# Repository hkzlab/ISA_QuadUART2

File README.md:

# ISA Quad UART Adapter (2 + 2)

## Introduction

This 8-bit ISA board will provide 4 serial RS232 ports using a single 16C554 controller.

Port 1 and 2 are exposed on the bracked as DB9 male connectors. Port 3 and 4 are internal.

IRQs will be shared between port 1/3 and port 2/4.

### Disclaimer

I take NO responsibility for what happens if you decide to build and use this card. Your computer might crash, catch fire or be destroyed in other nasty ways.
You're encourauged to take what you deem fit from this, and use it in your projects!

## Configuration

This board is configured via two blocks of jumpers:

```text
    .... SER4 
    ....
    .... SER3
IIII2323
RRRREEFF
QQQQ8888
3457
........ SER2
........
........ SER1
```

The upper block will select the address for port 3 (first row) and port 4 (third row). To select an address, you need to bridge the middle row at the specified address with the top or bottom row (depending on which port you wish to assign that address).

The bottom block selects the address for ports 1 and 2, and the IRQs for ports 1/3 and 2/4. The principle is the same.

Default configuration is as follow:
```text
    |... SER4 
    ||..
    .|.. SER3
IIII2323
RRRREEFF
QQQQ8888
3457
|.....|. SER2
||....||
.|.....| SER1
```

Which will assign 0x3F8 to port 1, 0x2F8 to port 2, 0x3E8 to port 3 and 0x2E8 to port 4.
Port 1/3 will get IRQ4 and port 2/4 will get IRQ3.

## Bill of Materials

- 4x 10uF / 25v capacitors
- 13x 100nF / 25v ceramic capacitors
- 1x 9-pin 10k bussed resistor network (RN3)
- 1x 5-pin 10k bussed resistor network (RN2)
- 1x 1.8432Mhz DIP14 or DIP8 oscillator
- 2x DB9 right angle, male, PCB mount connector
- 1x 1x20pin 2.54mm straight header strip (you will cut this as needed)
- 1x 2x20pin 2.54mm straight header strip (you will cut this as needed)
- 1x 2x20pin 2.54mm angled header strip (you will cut this as needed)
- 4x 75C185 RS232 drivers (U5, U6, U25, U26)
- 2x 74HCT138 (U1, U2)
- 1x 74HCT32 (U24)
- 1x 74HCT21 (U30)
- 1x 74HCT245 (U29) (with some controllers, like TL16C554, I noticed improved stability by using a 74LS245)
- 1x SC16C654, ST16C554 (U23) (all the 16C554 / 16C654 should be compatible, but to get TL16C554 working properly I had to replace U29) 
- Jumpers for board configuration
- Keystone 9200-15 bracket
- 1x PLCC68 THT socket
 
## Credits

- Thanks to [@A-Small-Mice](https://github.com/A-Small-Mice) for the printable bracket

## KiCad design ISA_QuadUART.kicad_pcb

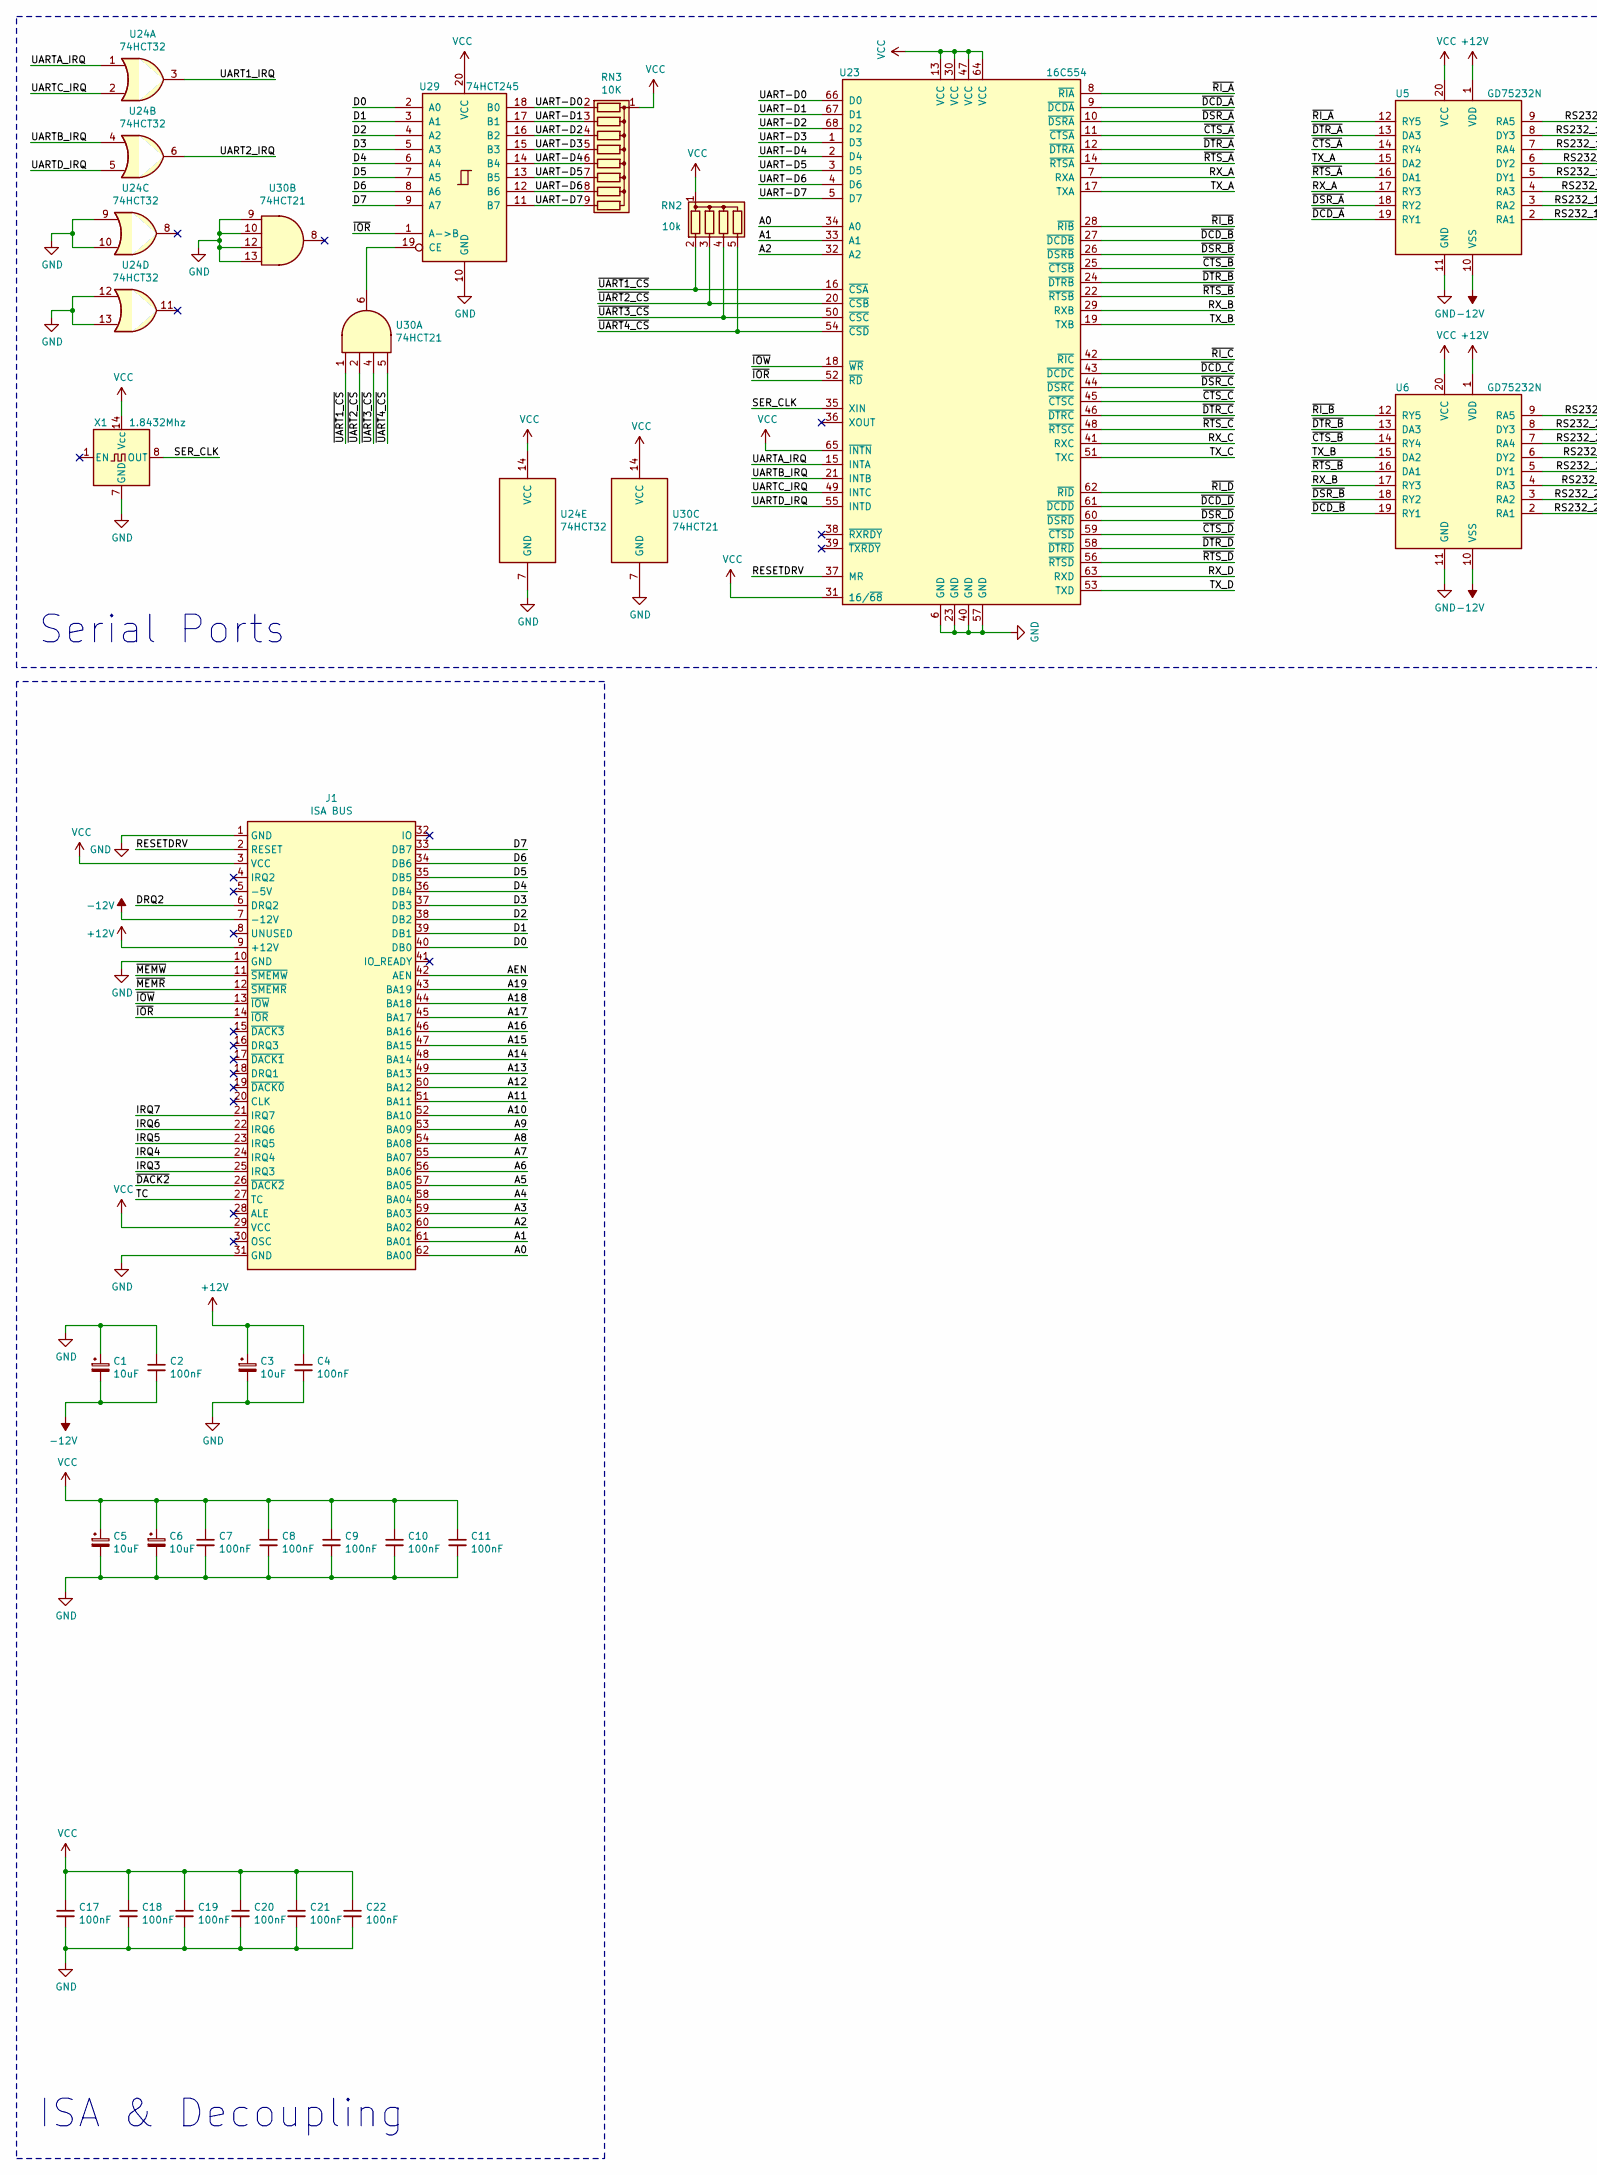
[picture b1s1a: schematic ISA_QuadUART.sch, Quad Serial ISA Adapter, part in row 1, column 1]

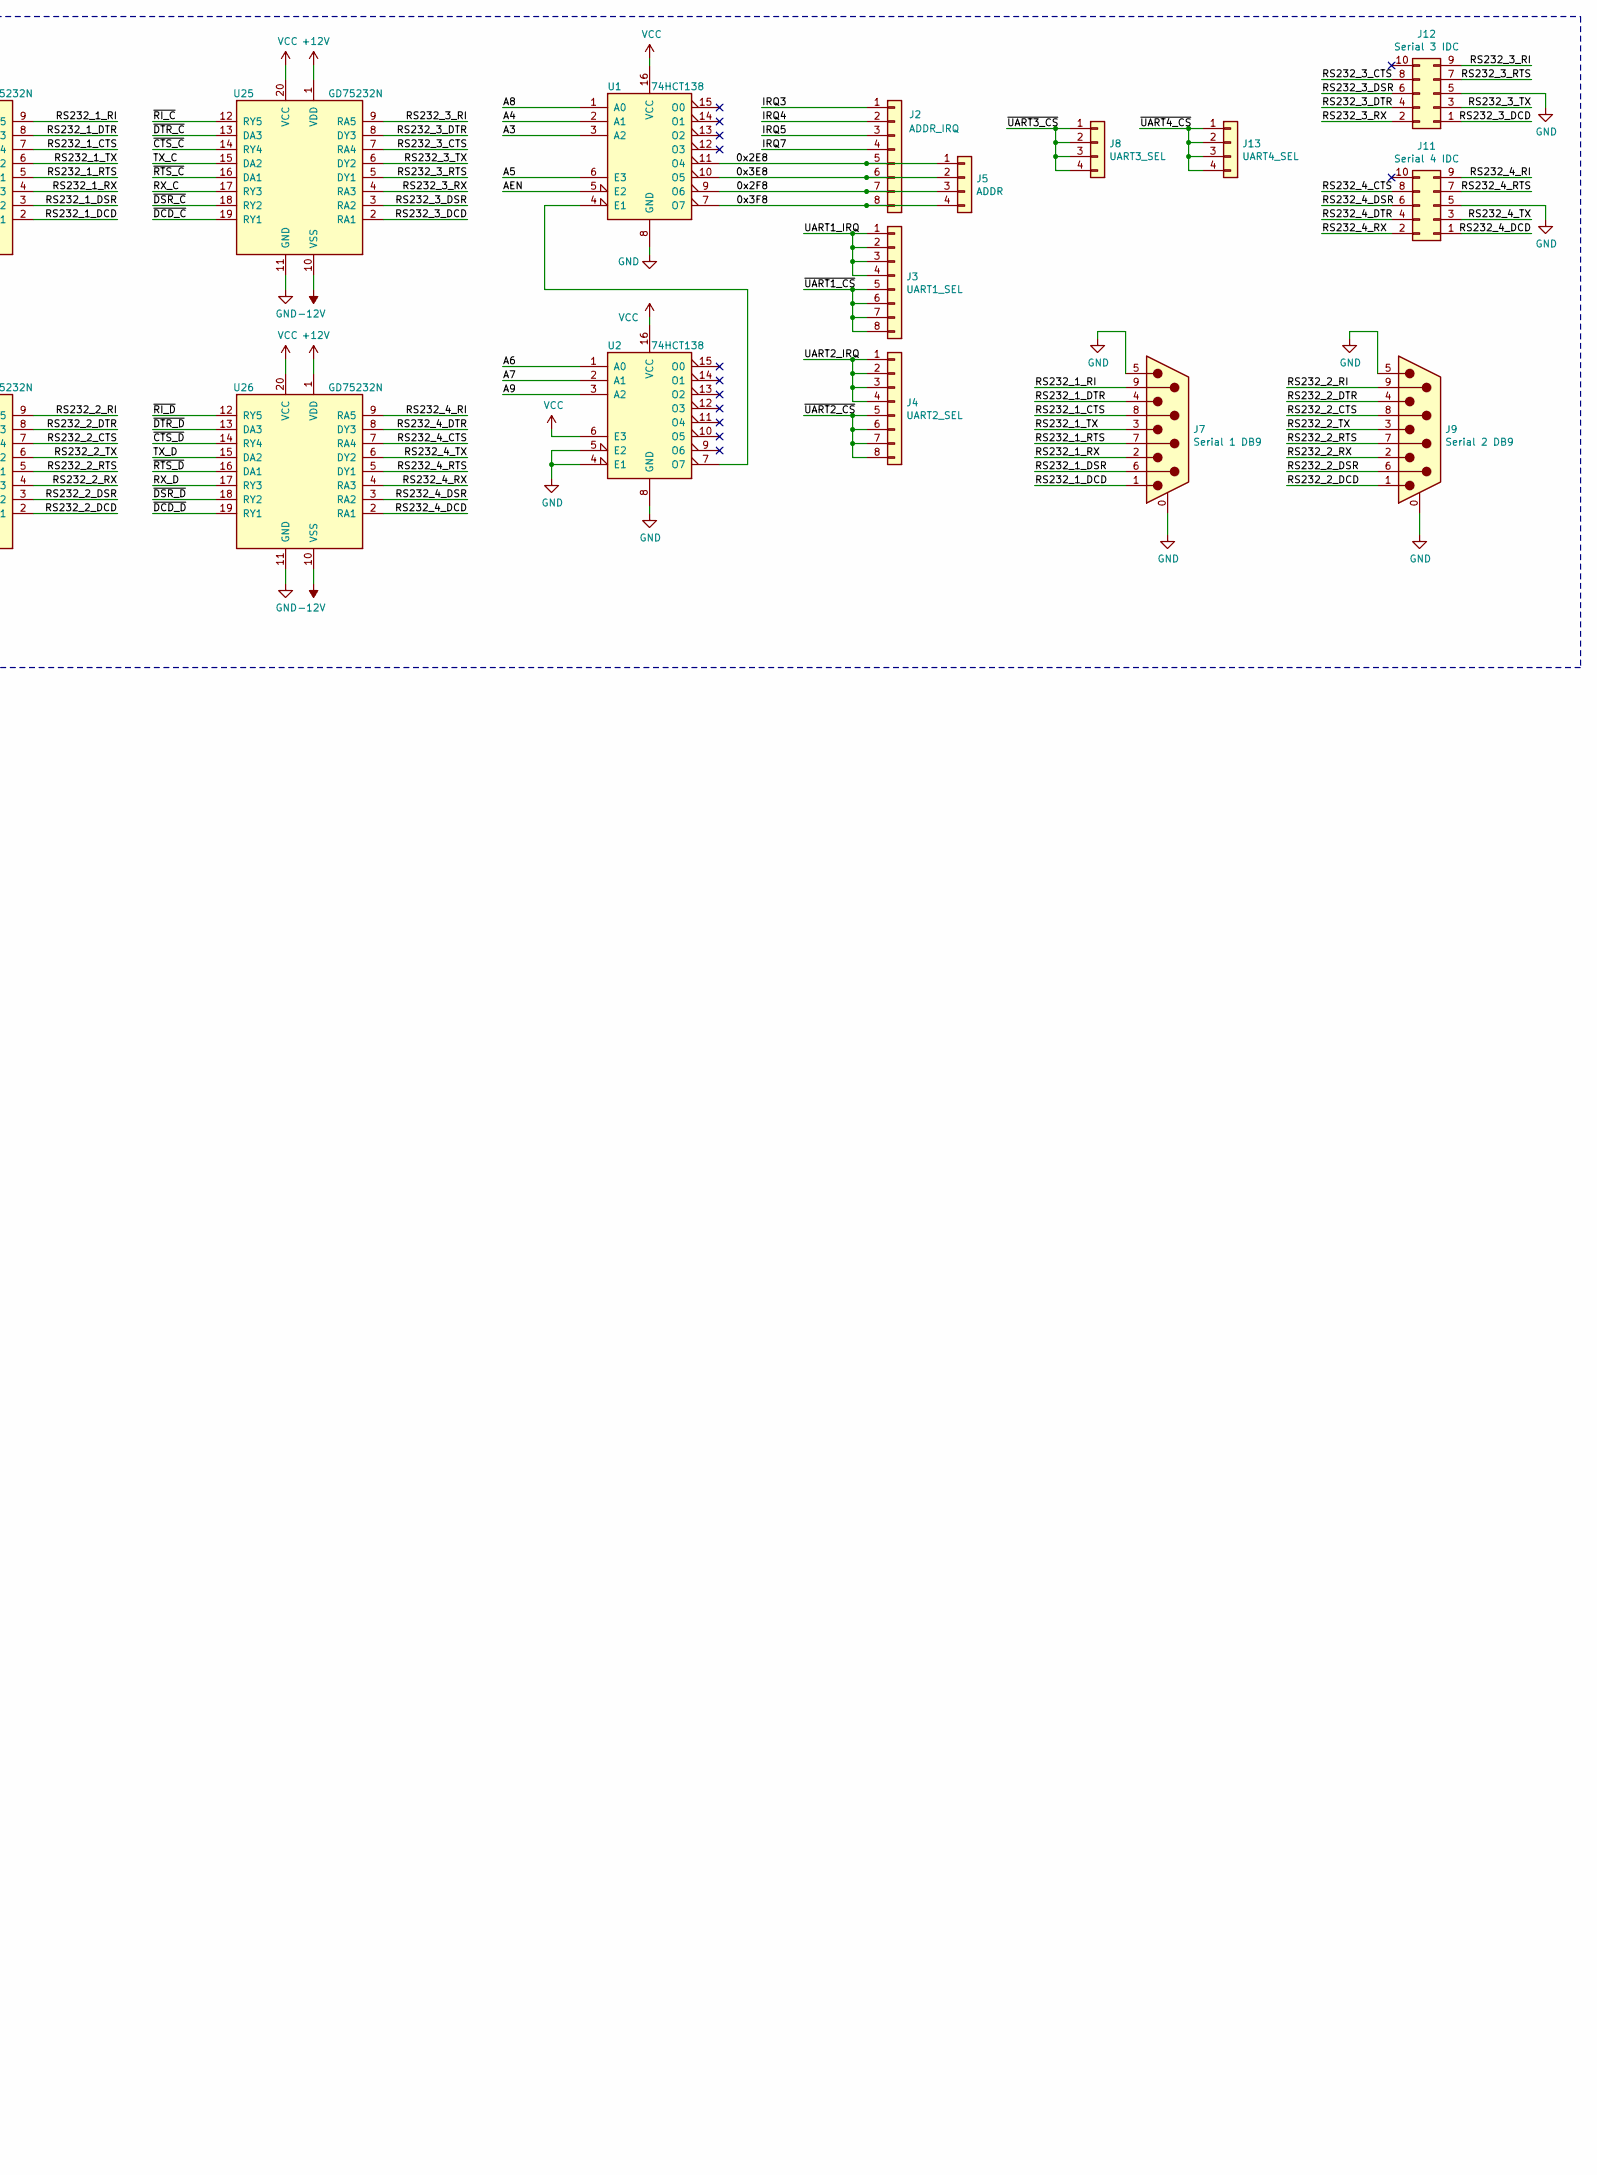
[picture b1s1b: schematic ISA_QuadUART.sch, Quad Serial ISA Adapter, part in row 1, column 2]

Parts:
C1, C3, C5, C6: 10uF; CP_Radial_D5.0mm_P2.50mm
C2, C4, C7, C8, C9, C10, C11, C17, C18, C19, C20, C21, C22: 100nF; C_Disc_D6.0mm_W2.5mm_P5.00mm
J1: ISA BUS; Conn_Edge_PCB_ISA8
J2: ADDR_IRQ; PinHeader_1x08_P2.54mm_Vertical
J3: UART1_SEL; PinHeader_1x08_P2.54mm_Vertical
J4: UART2_SEL; PinHeader_1x08_P2.54mm_Vertical
J5: ADDR; PinHeader_1x04_P2.54mm_Vertical
J7: Serial 1 DB9; DSUB-9_Male_Horizontal_P2.77x2.84mm_EdgePinOffset7.70mm_Hou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
J8: UART3_SEL; PinHeader_1x04_P2.54mm_Vertical
J9: Serial 2 DB9; DSUB-9_Male_Horizontal_P2.77x2.84mm_EdgePinOffset7.70mm_Hou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
J11: Serial 4 IDC; PinHeader_2x05_P2.54mm_Vertical
J12: Serial 3 IDC; PinHeader_2x05_P2.54mm_Vertical
J13: UART4_SEL; PinHeader_1x04_P2.54mm_Vertical
RN2: 10k; R_Array_SIP5
RN3: 10K; R_Array_SIP9
U1, U2: 74HCT138; DIP-16_W7.62mm_LongPads
U5, U6, U25, U26: GD75232N; DIP-20_W7.62mm_LongPads
U23: 16C554; PLCC-68_THT-Socket
U24: 74HCT32; DIP-14_W7.62mm_LongPads
U29: 74HCT245; DIP-20_W7.62mm_LongPads
U30: 74HCT21; DIP-14_W7.62mm_LongPads
X1: 1.8432Mhz; Oscillator_DIP-14-8

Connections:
+12V: C3.1, C4.1, J1.9 (+12V), U5.1 (VDD), U6.1 (VDD), U25.1 (VDD), U26.1 (VDD)
-12V: C1.2, C2.2, J1.7 (-12V), U5.10 (VSS), U6.10 (VSS), U25.10 (VSS), U26.10 (VSS)
/0x2E8: J2.5, J5.1, U1.11 (O4)
/0x2F8: J2.7, J5.3, U1.9 (O6)
/0x3E8: J2.6, J5.2, U1.10 (O5)
/0x3F8: J2.8, J5.4, U1.7 (O7)
/A0: J1.62 (BA00), U23.34 (A0)
/A1: J1.61 (BA01), U23.33 (A1)
/A2: J1.60 (BA02), U23.32 (A2)
/A3: J1.59 (BA03), U1.3 (A2)
/A4: J1.58 (BA04), U1.2 (A1)
/A5: J1.57 (BA05), U1.6 (E3)
/A6: J1.56 (BA06), U2.1 (A0)
/A7: J1.55 (BA07), U2.2 (A1)
/A8: J1.54 (BA08), U1.1 (A0)
/A9: J1.53 (BA09), U2.3 (A2)
/A10: J1.52 (BA10)
/A11: J1.51 (BA11)
/A12: J1.50 (BA12)
/A13: J1.49 (BA13)
/A14: J1.48 (BA14)
/A15: J1.47 (BA15)
/A16: J1.46 (BA16)
/A17: J1.45 (BA17)
/A18: J1.44 (BA18)
/A19: J1.43 (BA19)
/AEN: J1.42 (AEN), U1.5 (E2)
/D0: J1.40 (DB0), U29.2 (A0)
/D1: J1.39 (DB1), U29.3 (A1)
/D2: J1.38 (DB2), U29.4 (A2)
/D3: J1.37 (DB3), U29.5 (A3)
/D4: J1.36 (DB4), U29.6 (A4)
/D5: J1.35 (DB5), U29.7 (A5)
/D6: J1.34 (DB6), U29.8 (A6)
/D7: J1.33 (DB7), U29.9 (A7)
/DRQ2: J1.6 (DRQ2)
/IRQ3: J1.25 (IRQ3), J2.1
/IRQ4: J1.24 (IRQ4), J2.2
/IRQ5: J1.23 (IRQ5), J2.3
/IRQ6: J1.22 (IRQ6)
/IRQ7: J1.21 (IRQ7), J2.4
/RESETDRV: J1.2 (RESET), U23.37 (MR)
/RS232_1_CTS: J7.8, U5.7 (RA4)
/RS232_1_DCD: J7.1, U5.2 (RA1)
/RS232_1_DSR: J7.6, U5.3 (RA2)
/RS232_1_DTR: J7.4, U5.8 (DY3)
/RS232_1_RI: J7.9, U5.9 (RA5)
/RS232_1_RTS: J7.7, U5.5 (DY1)
/RS232_1_RX: J7.2, U5.4 (RA3)
/RS232_1_TX: J7.3, U5.6 (DY2)
/RS232_2_CTS: J9.8, U6.7 (RA4)
/RS232_2_DCD: J9.1, U6.2 (RA1)
/RS232_2_DSR: J9.6, U6.3 (RA2)
/RS232_2_DTR: J9.4, U6.8 (DY3)
/RS232_2_RI: J9.9, U6.9 (RA5)
/RS232_2_RTS: J9.7, U6.5 (DY1)
/RS232_2_RX: J9.2, U6.4 (RA3)
/RS232_2_TX: J9.3, U6.6 (DY2)
/RS232_3_CTS: J12.8, U25.7 (RA4)
/RS232_3_DCD: J12.1, U25.2 (RA1)
/RS232_3_DSR: J12.6, U25.3 (RA2)
/RS232_3_DTR: J12.4, U25.8 (DY3)
/RS232_3_RI: J12.9, U25.9 (RA5)
/RS232_3_RTS: J12.7, U25.5 (DY1)
/RS232_3_RX: J12.2, U25.4 (RA3)
/RS232_3_TX: J12.3, U25.6 (DY2)
/RS232_4_CTS: J11.8, U26.7 (RA4)
/RS232_4_DCD: J11.1, U26.2 (RA1)
/RS232_4_DSR: J11.6, U26.3 (RA2)
/RS232_4_DTR: J11.4, U26.8 (DY3)
/RS232_4_RI: J11.9, U26.9 (RA5)
/RS232_4_RTS: J11.7, U26.5 (DY1)
/RS232_4_RX: J11.2, U26.4 (RA3)
/RS232_4_TX: J11.3, U26.6 (DY2)
/RX_A: U5.17 (RY3), U23.7 (RXA)
/RX_B: U6.17 (RY3), U23.29 (RXB)
/RX_C: U23.41 (RXC), U25.17 (RY3)
/RX_D: U23.63 (RXD), U26.17 (RY3)
/SER_CLK: U23.35 (XIN), X1.8 (OUT)
/TC: J1.27 (TC)
/TX_A: U5.15 (DA2), U23.17 (TXA)
/TX_B: U6.15 (DA2), U23.19 (TXB)
/TX_C: U23.51 (TXC), U25.15 (DA2)
/TX_D: U23.53 (TXD), U26.15 (DA2)
/UART1_IRQ: J3.1, J3.2, J3.3, J3.4, U24.3
/UART2_IRQ: J4.1, J4.2, J4.3, J4.4, U24.6
/UART-D0: RN3.2 (R1), U23.66 (D0), U29.18 (B0)
/UART-D1: RN3.3 (R2), U23.67 (D1), U29.17 (B1)
/UART-D2: RN3.4 (R3), U23.68 (D2), U29.16 (B2)
/UART-D3: RN3.5 (R4), U23.1 (D3), U29.15 (B3)
/UART-D4: RN3.6 (R5), U23.2 (D4), U29.14 (B4)
/UART-D5: RN3.7 (R6), U23.3 (D5), U29.13 (B5)
/UART-D6: RN3.8 (R7), U23.4 (D6), U29.12 (B6)
/UART-D7: RN3.9 (R8), U23.5 (D7), U29.11 (B7)
/UARTA_IRQ: U23.15 (INTA), U24.1
/UARTB_IRQ: U23.21 (INTB), U24.4
/UARTC_IRQ: U23.49 (INTC), U24.2
/UARTD_IRQ: U23.55 (INTD), U24.5
/~CTS_A: U5.14 (RY4), U23.11 (~CTSA)
/~CTS_B: U6.14 (RY4), U23.25 (~CTSB)
/~CTS_C: U23.45 (~CTSC), U25.14 (RY4)
/~CTS_D: U23.59 (~CTSD), U26.14 (RY4)
/~DACK2: J1.26 (~DACK2)
/~DCD_A: U5.19 (RY1), U23.9 (~DCDA)
/~DCD_B: U6.19 (RY1), U23.27 (~DCDB)
/~DCD_C: U23.43 (~DCDC), U25.19 (RY1)
/~DCD_D: U23.61 (~DCDD), U26.19 (RY1)
/~DSR_A: U5.18 (RY2), U23.10 (~DSRA)
/~DSR_B: U6.18 (RY2), U23.26 (~DSRB)
/~DSR_C: U23.44 (~DSRC), U25.18 (RY2)
/~DSR_D: U23.60 (~DSRD), U26.18 (RY2)
/~DTR_A: U5.13 (DA3), U23.12 (~DTRA)
/~DTR_B: U6.13 (DA3), U23.24 (~DTRB)
/~DTR_C: U23.46 (~DTRC), U25.13 (DA3)
/~DTR_D: U23.58 (~DTRD), U26.13 (DA3)
/~IOR: J1.14 (~IOR), U23.52 (~RD~), U29.1 (A->B)
/~IOW: J1.13 (~IOW), U23.18 (~WR~)
/~MEMR: J1.12 (~SMEMR)
/~MEMW: J1.11 (~SMEMW)
/~RI_A: U5.12 (RY5), U23.8 (~RIA)
/~RI_B: U6.12 (RY5), U23.28 (~RIB)
/~RI_C: U23.42 (~RIC), U25.12 (RY5)
/~RI_D: U23.62 (~RID), U26.12 (RY5)
/~RTS_A: U5.16 (DA1), U23.14 (~RTSA)
/~RTS_B: U6.16 (DA1), U23.22 (~RTSB)
/~RTS_C: U23.48 (~RTSC), U25.16 (DA1)
/~RTS_D: U23.56 (~RTSD), U26.16 (DA1)
/~UART1_CS: J3.5, J3.6, J3.7, J3.8, RN2.2 (R1), U23.16 (~CSA), U30.1
/~UART2_CS: J4.5, J4.6, J4.7, J4.8, RN2.3 (R2), U23.20 (~CSB), U30.2
/~UART3_CS: J8.1, J8.2, J8.3, J8.4, RN2.4 (R3), U23.50 (~CSC), U30.4
/~UART4_CS: J13.1, J13.2, J13.3, J13.4, RN2.5 (R4), U23.54 (~CSD), U30.5
GND: C1.1, C2.1, C3.2, C4.2, C5.2, C6.2, C7.2, C8.2, C9.2, C10.2, C11.2, C17.2, C18.2, C19.2, C20.2, C21.2, C22.2, J1.1 (GND), J1.10 (GND), J1.31 (GND), J7.0 (PAD), J7.5, J9.0 (PAD), J9.5, J11.5, J12.5, U1.8 (GND), U2.4 (E1), U2.5 (E2), U2.8 (GND), U5.11 (GND), U6.11 (GND), U23.6 (GND), U23.23 (GND), U23.40 (GND), U23.57 (GND), U24.7 (GND), U24.9, U24.10, U24.12, U24.13, U25.11 (GND), U26.11 (GND), U29.10 (GND), U30.7 (GND), U30.9, U30.10, U30.12, U30.13, X1.7 (GND)
unnamed: U1.4 (E1), U2.7 (O7)
unnamed: U29.19 (CE), U30.6
VCC: C5.1, C6.1, C7.1, C8.1, C9.1, C10.1, C11.1, C17.1, C18.1, C19.1, C20.1, C21.1, C22.1, J1.3 (VCC), J1.29 (VCC), RN2.1 (common), RN3.1 (common), U1.16 (VCC), U2.6 (E3), U2.16 (VCC), U5.20 (VCC), U6.20 (VCC), U23.13 (VCC), U23.30 (VCC), U23.31 (16/~68), U23.47 (VCC), U23.64 (VCC), U23.65 (~INTN), U24.14 (VCC), U25.20 (VCC), U26.20 (VCC), U29.20 (VCC), U30.14 (VCC), X1.14 (Vcc)

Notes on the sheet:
Serial Ports
ISA & Decoupling

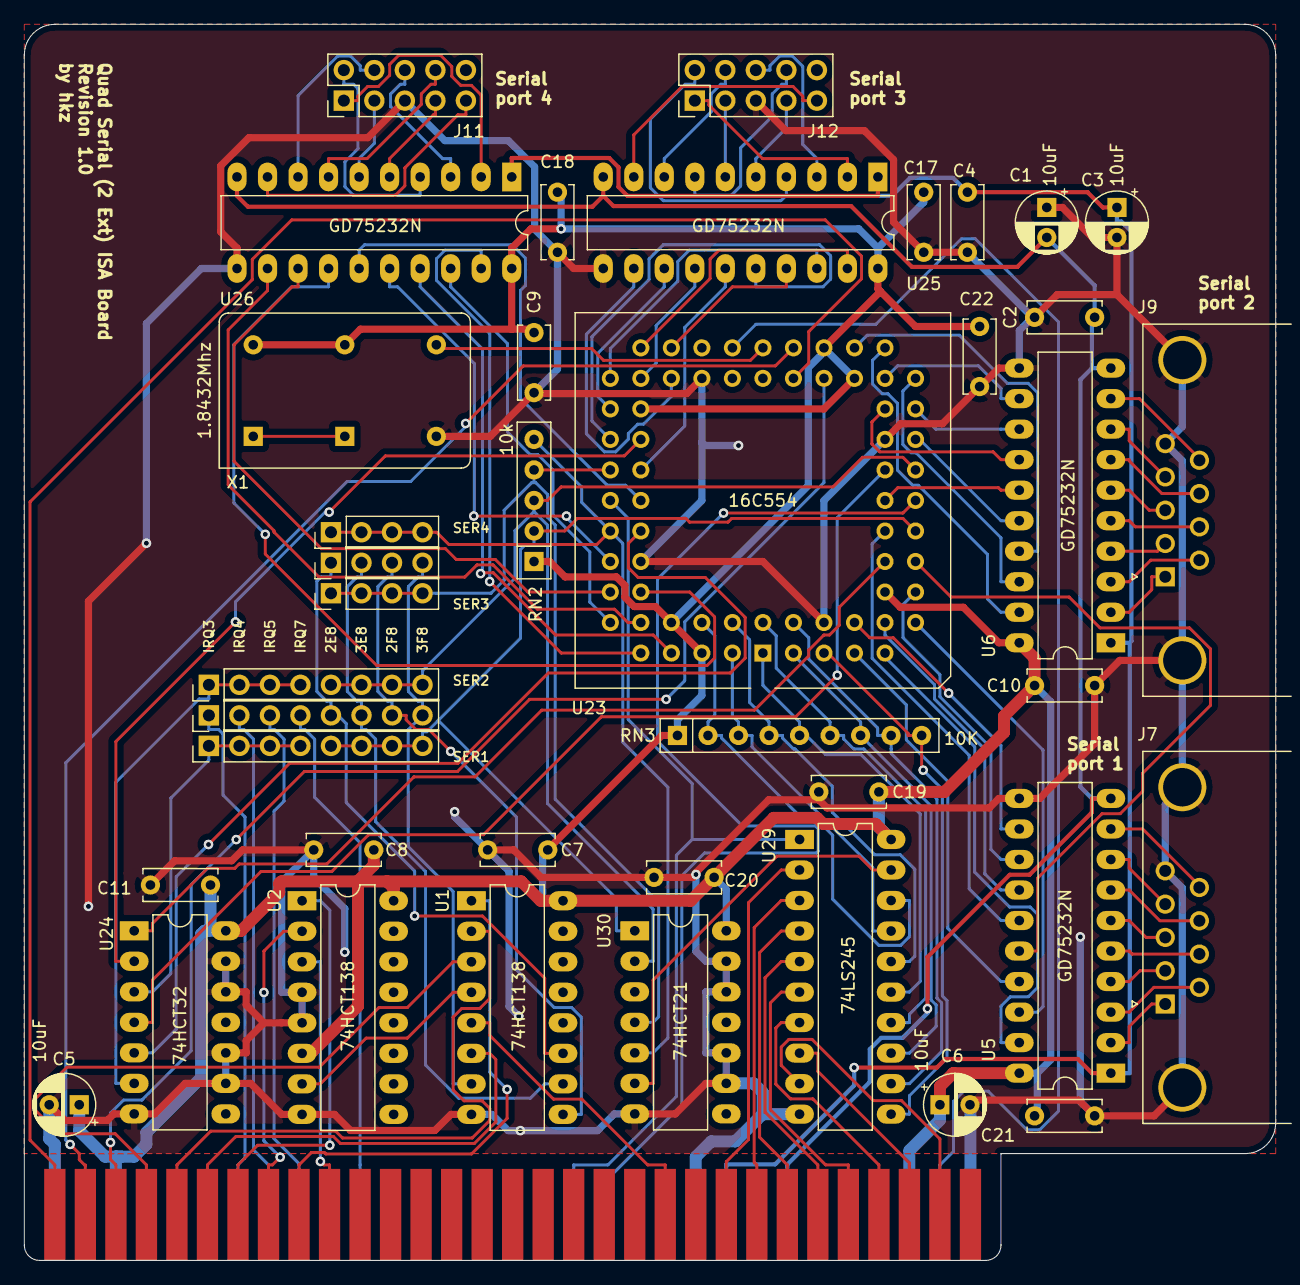
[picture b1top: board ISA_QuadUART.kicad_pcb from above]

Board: 2 copper layers, 104.1 x 102.9 mm, 41 parts (0 on the bottom side), 119 nets.

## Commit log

2021-02-20 Import older project
2021-02-20 Import lib
2021-02-20 Fix modules
2021-02-20 Fix paths
2021-02-20 Add 16C554
2021-02-20 Additional parallel ports
2021-02-20 Route Serial/Parallel/ROM board
2021-02-20 Fix silkscreen
2021-02-20 Add rev 1.0 gerbers
2021-02-20 Save gerber path
2021-02-22 Add notes to the schematic, cleaned the silkscreen
2021-02-23 Update mask and gerbers
2021-03-17 Update silkscreen
2021-03-18 set resistor type for '554 pullup to 4.7k
2021-03-18 Added LED bar and moved serial leds
2021-03-18 Mark pin 36 as unconnected
2021-03-19 Mark some active low signals as such in parport
2021-03-19 Remove ROM, add buffer for uart
2021-03-19 Add new gerber, use 74HCT21
2021-03-19 Slightly adjust the silkscreen
2021-03-19 Updated silkscreen, again
2021-03-20 Adjust silkscreen
2021-03-21 Add first revision of single quad uart
2021-03-21 rerouted pcb
2021-04-16 Added readme and pics
2021-04-16 Add license
2021-04-16 Add bracket in BOM
2021-04-16 Add component in BOM
2021-04-16 Add PLCC socket
2021-04-27 Add 2 external serial ports
2021-04-27 Removed gerbers from old board
2021-04-27 Move connectors
2021-04-27 Change ground plane on board
2021-04-28 Slight fixes to silkscreen
2021-04-28 Slightly better filling for ground plane
2021-04-28 Create gerbers
2021-05-25 Add footprint for keystone 9200-15
2021-06-20 Redone some power traces
2021-06-25 Update gerbers
2021-07-07 Add picture and update README
2021-11-09 Update Kicad url
2023-12-09 Add a 3D model for ISA_QuadUART2
2023-12-09 Add credits for the bracket
